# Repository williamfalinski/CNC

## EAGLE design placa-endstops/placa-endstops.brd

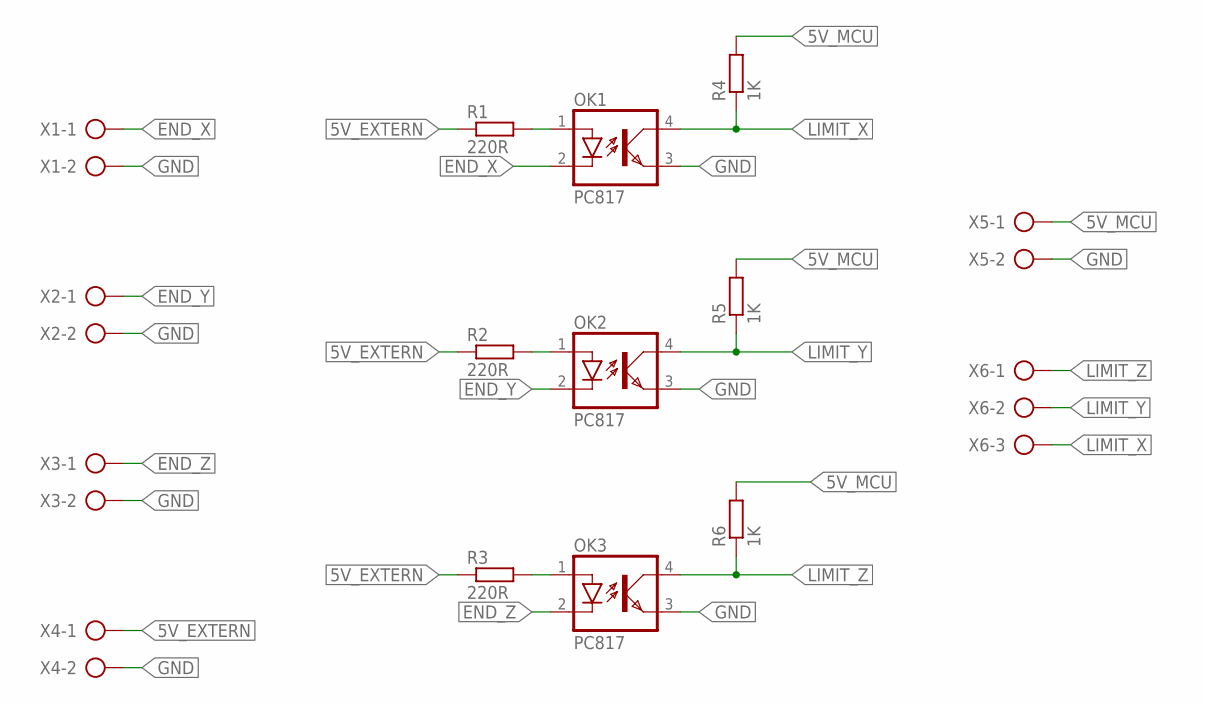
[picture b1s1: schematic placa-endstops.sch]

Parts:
OK1, OK2, OK3: PC817; DIL04
R1, R2, R3: 220R; 0207/10
R4, R5, R6: 1K; 0207/10
X1, X2, X3, X4, X5: AK500/2
X6: AK500/3

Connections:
5V_EXTERN: R1.1, R2.1, R3.1, X4.1
5V_MCU: R4.2, R5.2, R6.2, X5.1
END_X: OK1.2 (C), X1.1
END_Y: OK2.2 (C), X2.1
END_Z: OK3.2 (C), X3.1
GND: OK1.3 (EMIT), OK2.3 (EMIT), OK3.3 (EMIT), X1.2, X2.2, X3.2, X4.2, X5.2
LIMIT_X: OK1.4 (COL), R4.1, X6.3
LIMIT_Y: OK2.4 (COL), R5.1, X6.2
LIMIT_Z: OK3.4 (COL), R6.1, X6.1
unnamed: OK1.1 (A), R1.2
unnamed: OK2.1 (A), R2.2
unnamed: OK3.1 (A), R3.2

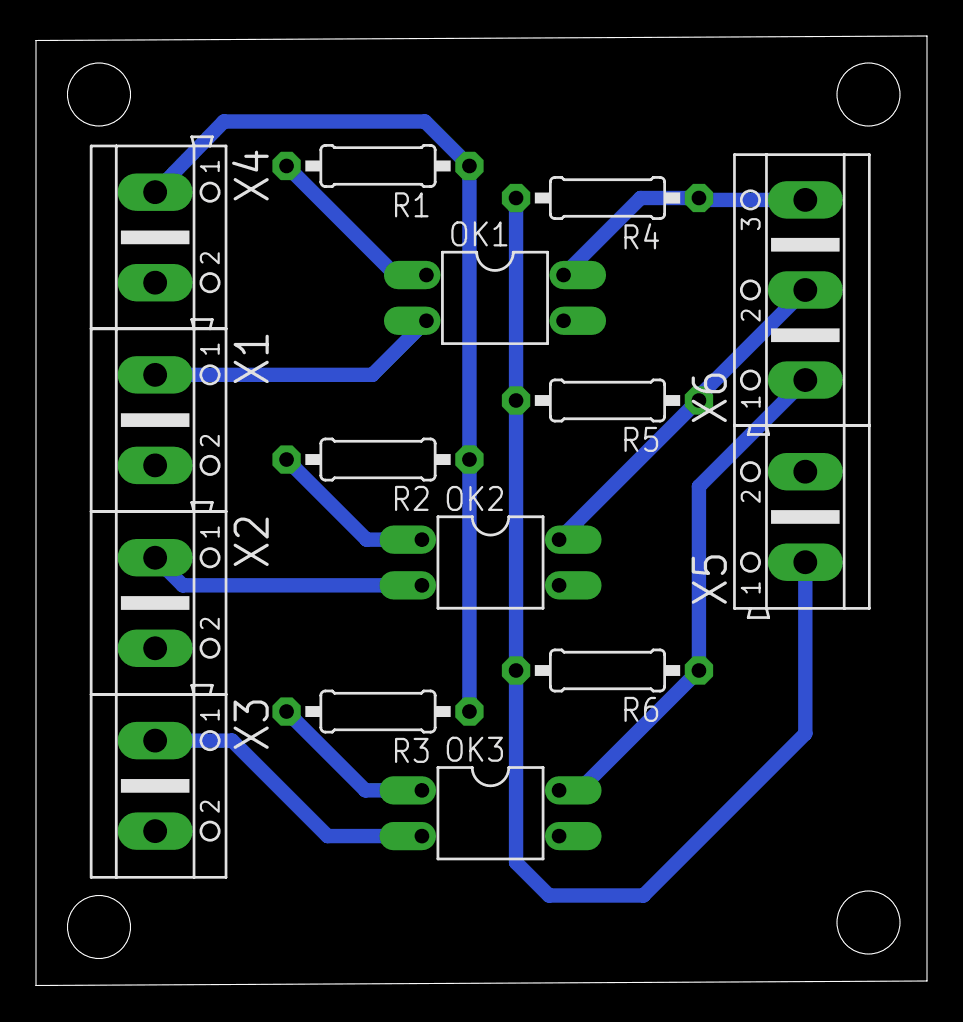
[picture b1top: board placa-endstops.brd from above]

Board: 2 copper layers, 49.5 x 52.8 mm, 15 parts (0 on the bottom side), 12 nets.

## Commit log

2020-09-01 Placa endstops
